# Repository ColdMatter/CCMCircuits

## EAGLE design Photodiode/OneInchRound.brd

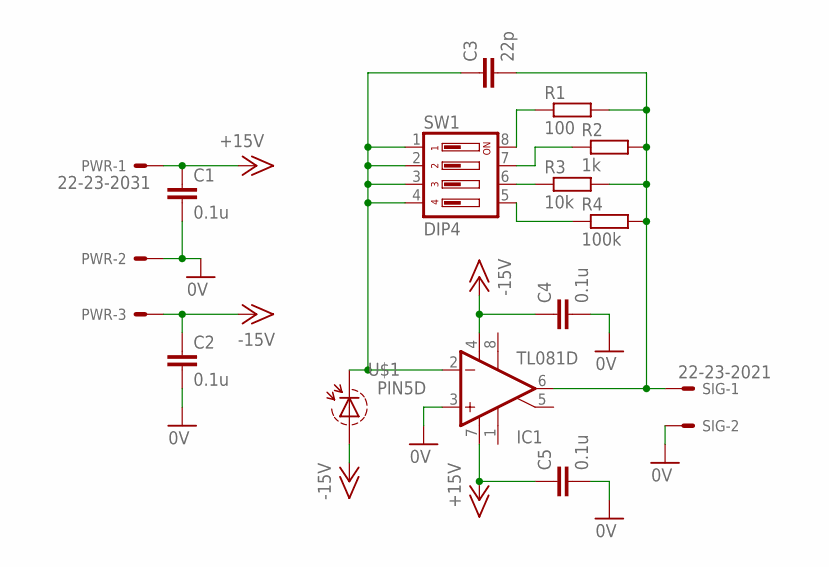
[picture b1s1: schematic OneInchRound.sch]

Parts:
C1, C2, C4, C5: 0.1u; C0805
C3: 22p; C0805
IC1: TL081D; SO08
PWR: 22-23-2031
R1: 100; R0805
R2: 1k; R0805
R3: 10k; R0805
R4: 100k; R0805
SIG: 22-23-2021
SW1: DIP4; SO08
U$1: PIN5D; TO5_2P

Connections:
0V: C1.2, C2.2, C4.2, C5.2, IC1.3 (+IN), PWR.2, SIG.2
+15V: C1.1, C5.1, IC1.7 (V+), PWR.1
-15V: C2.1, C4.1, IC1.4 (V-), PWR.3, U$1.1 (ANODE)
unnamed: C3.1, IC1.2 (-IN), SW1.1, SW1.2, SW1.3, SW1.4, U$1.3 (CATH)
unnamed: C3.2, IC1.6 (OUT), R1.2, R2.2, R3.2, R4.2, SIG.1
unnamed: R3.1, SW1.6
unnamed: R4.1, SW1.5
unnamed: R2.1, SW1.7
unnamed: R1.1, SW1.8

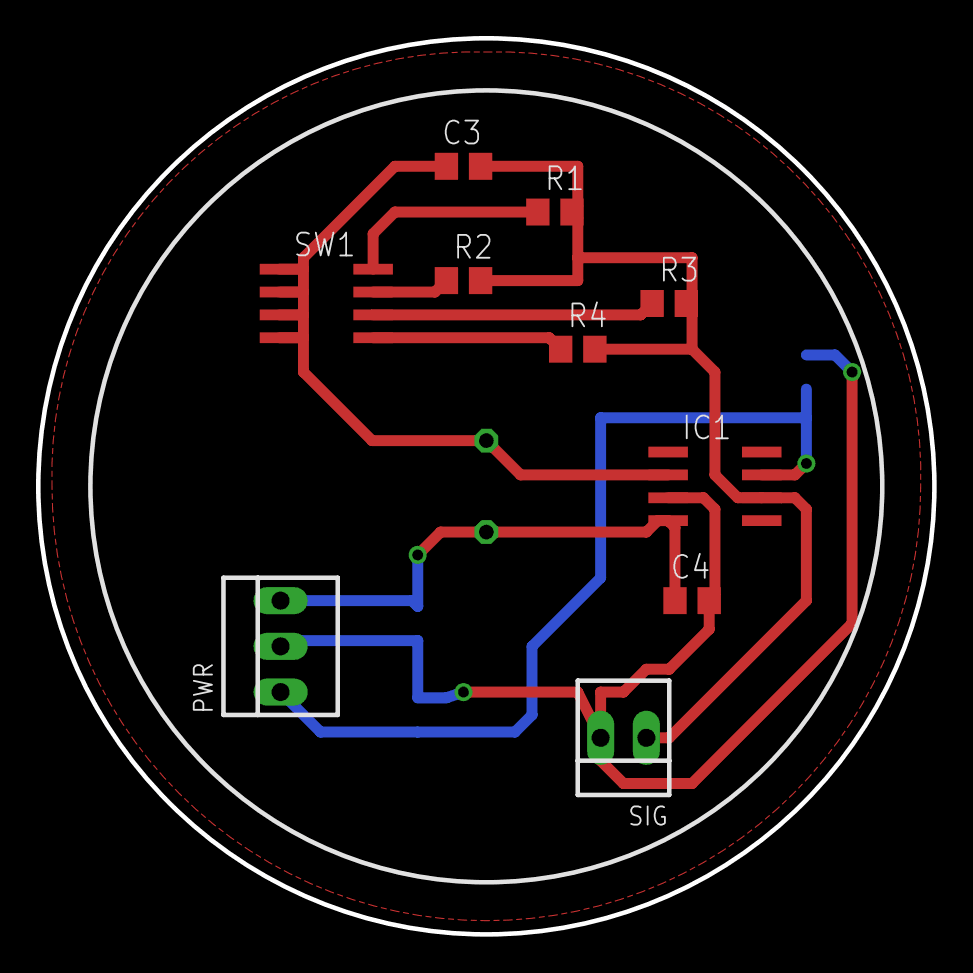
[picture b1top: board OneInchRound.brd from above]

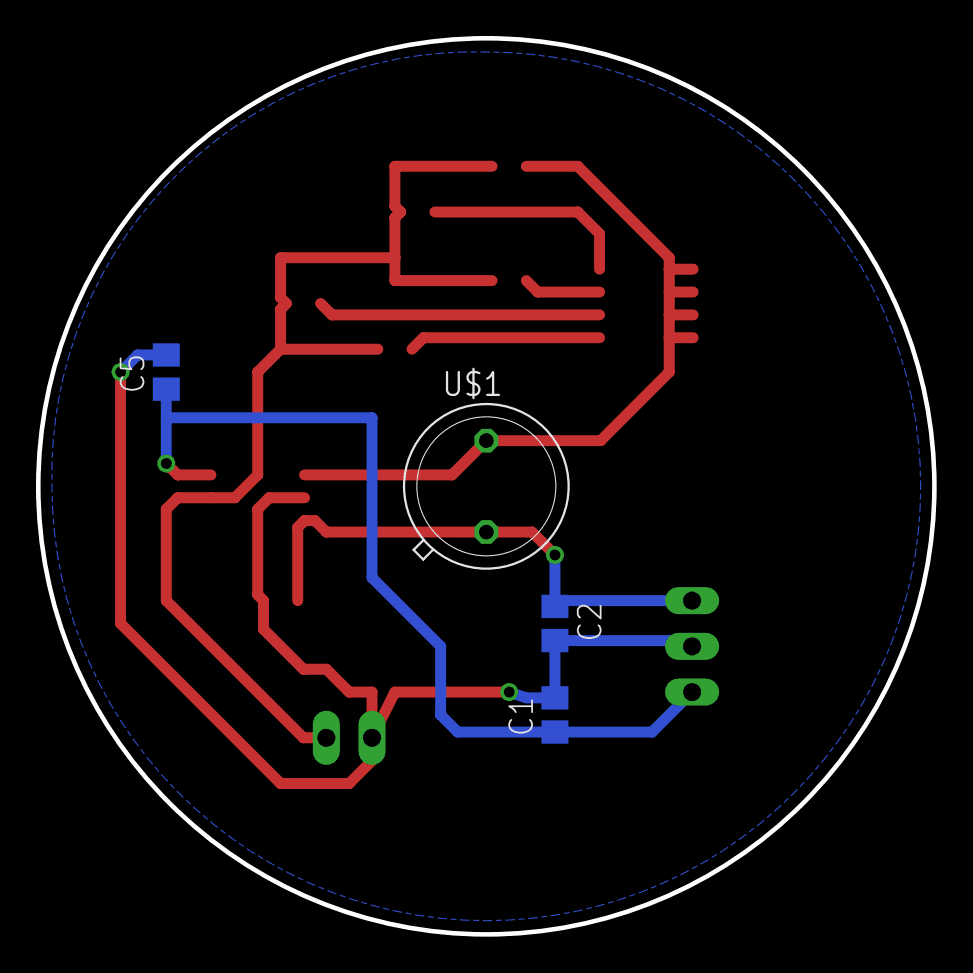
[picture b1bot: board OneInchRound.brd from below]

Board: 2 copper layers, 49.8 x 49.8 mm, 14 parts (4 on the bottom side), 9 nets.

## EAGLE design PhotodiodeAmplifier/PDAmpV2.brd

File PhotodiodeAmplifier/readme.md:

Photodiode Amplifier

This is a simple circuit to amplify a photodiode signal.

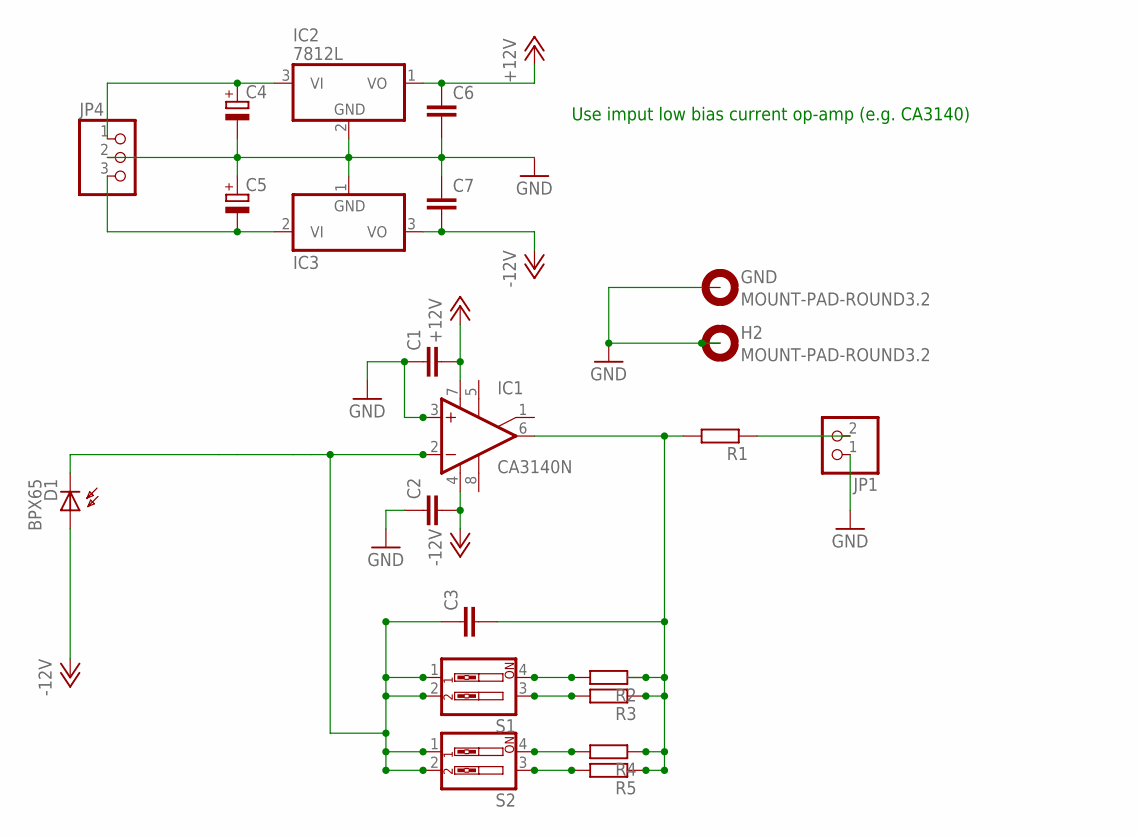
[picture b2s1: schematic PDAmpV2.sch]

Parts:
C1, C2: C-EU025-025X050; C025-025X050
C3, C6, C7: C-EU050-030X075; C050-030X075
C4, C5: CPOL-EUE5-8.5; E5-8,5
D1: BPX65
GND: MOUNT-PAD-ROUND3.2; 3,2-PAD
H2: MOUNT-PAD-ROUND3.2; 3,2-PAD
IC1: CA3140N; DIL08
IC2: 7812L; TO92
IC3: 7912L; TO92
JP1: PINHD-1X2; 1X02
JP4: PINHD-1X3; 1X03
R1, R2, R3, R4, R5: R-EU_0207/10; 0207/10
S1, S2: SW_DIP-2; EDG-02

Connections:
+12V: C1.2, C6.1, IC1.7 (V+), IC2.1 (VO)
-12V: C2.2, C7.2, D1.A, IC1.4 (V-), IC3.3 (VO)
GND: C1.1, C2.1, C4.-, C5.+, C6.2, C7.1, GND.B3,2, H2.B3,2, IC1.3 (+IN), IC2.2 (GND), IC3.1 (GND), JP1.1, JP4.2
unnamed: C3.1, D1.K (C), IC1.2 (-IN), S1.1, S1.2, S2.1, S2.2
unnamed: C4.+, IC2.3 (VI), JP4.1
unnamed: C5.-, IC3.2 (VI), JP4.3
unnamed: JP1.2, R1.1
unnamed: R2.2, S1.4
unnamed: R3.2, S1.3
unnamed: R4.2, S2.4
unnamed: R5.2, S2.3
unnamed: C3.2, IC1.6 (OUT), R1.2, R2.1, R3.1, R4.1, R5.1

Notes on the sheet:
Use imput low bias current op-amp (e.g. CA3140)

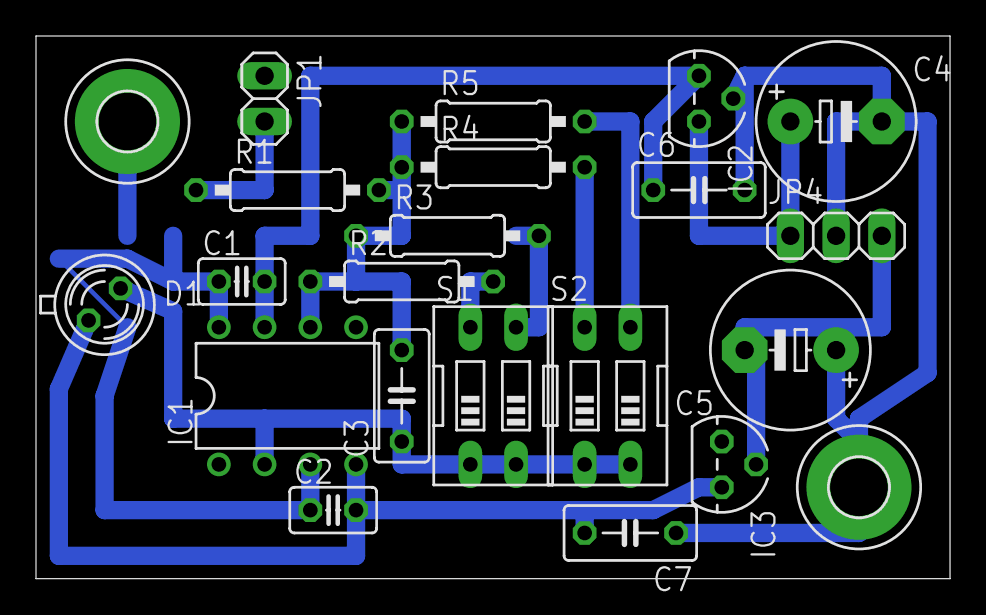
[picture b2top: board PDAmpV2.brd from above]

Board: 2 copper layers, 50.8 x 30.1 mm, 22 parts (0 on the bottom side), 12 nets.

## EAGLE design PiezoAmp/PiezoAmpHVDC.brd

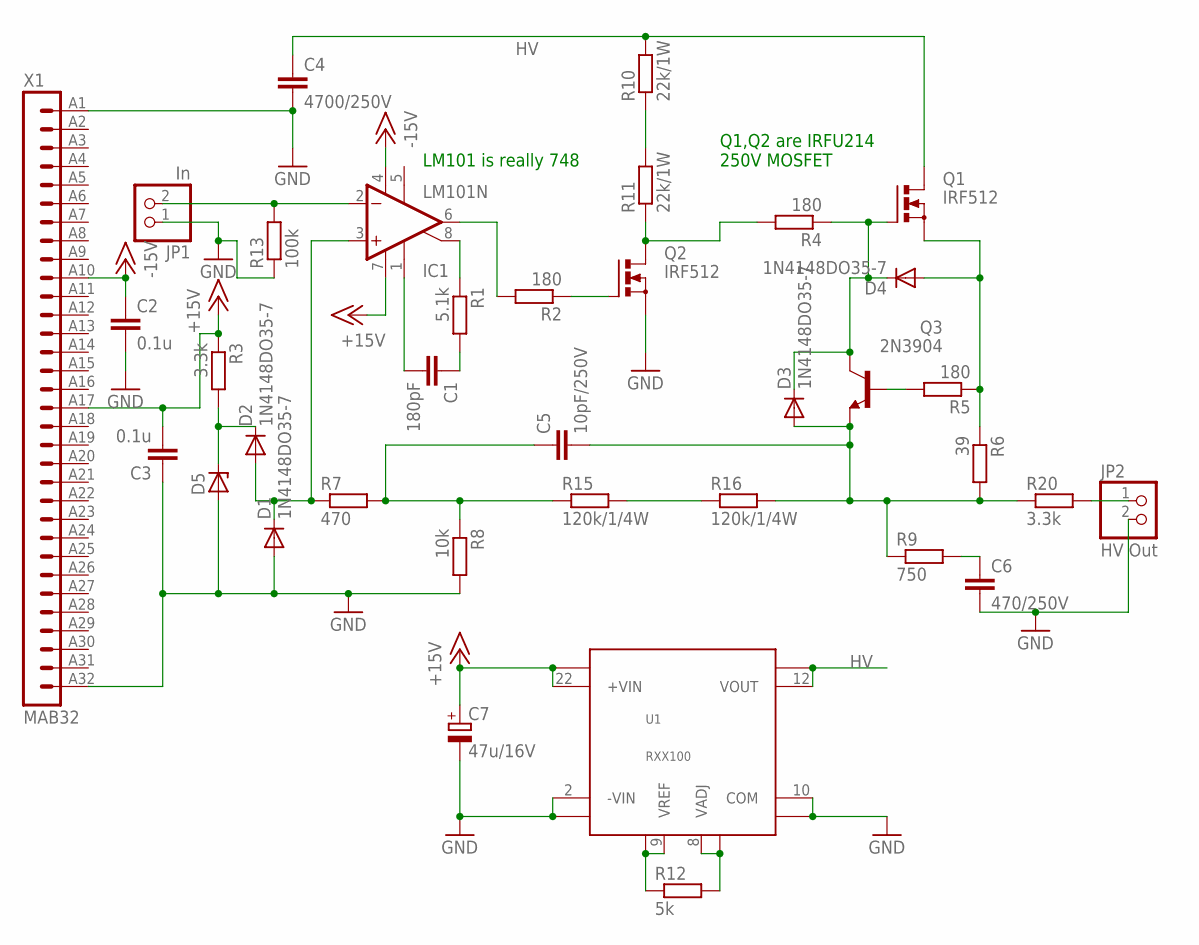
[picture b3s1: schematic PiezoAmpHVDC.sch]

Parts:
C1: 180pF; C050-030X075
C2, C3: 0.1u; C050-030X075
C4: 4700/250V; C075-032X103
C5: 10pF/250V; C075-032X103
C6: 470/250V; C075-032X103
C7: 47u/16V; SANYO-OSCON_F8
D1, D2, D3, D4: 1N4148DO35-7; DO35-7
D5: ZENER-DIODEDO34-7; DO34Z7
IC1: LM101N; DIL08
JP1: In; 1X02
JP2: HV Out; 1X02
Q1, Q2: IRF512; TO220BV
Q3: 2N3904; TO92
R1: 5.1k; 0204/7
R2, R4, R5: 180; 0204/7
R3, R20: 3.3k; 0204/7
R6: 39; 0204/7
R7: 470; 0204/7
R8: 10k; 0204/7
R9: 750; 0204/7
R10, R11: 22k/1W; 0411/15
R12: 5k; 0204/7
R13: 100k; 0204/5
R15, R16: 120k/1/4W; 0411/15
U1: RXX100; RXXDIP
X1: MAB32

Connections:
+15V: C3.2, C7.+, IC1.7 (V+), R3.1, U1.22 (+VIN), U1.23 (VIN2+), X1.A17 (17)
-15V: C2.1, IC1.4 (V-), X1.A10 (10)
GND: C2.2, C3.1, C4.2, C6.2, C7.-, D1.A, D5.A, JP1.1, JP2.2, Q2.S, R8.2, R13.1, U1.2 (-VIN), U1.3 (VIN2-), U1.10 (COM), U1.15 (COM2), X1.A1 (1), X1.A32 (32)
HV: C4.1, Q1.D, R10.2, U1.12 (VOUT), U1.13 (VOUT2)
unnamed: IC1.2 (-IN), JP1.2, R13.2
unnamed: R10.1, R11.2
unnamed: Q2.G, R2.1
unnamed: Q2.D, R4.2, R11.1
unnamed: C6.1, R9.2
unnamed: R12.2, U1.8 (VADJ), U1.17 (VADJ2)
unnamed: IC1.8 (ON2), R1.1
unnamed: IC1.6 (OUT), R2.2
unnamed: R12.1, U1.9 (VREF), U1.16 (VREF2)
unnamed: D3.C, D4.C, Q1.G, Q3.1 (C), R4.1
unnamed: D4.A, Q1.S, R5.1, R6.1
unnamed: Q3.2 (B), R5.2
unnamed: C5.2, D3.A, Q3.3 (E), R6.2, R9.1, R16.2, R20.1
unnamed: R15.2, R16.1
unnamed: C5.1, R7.2, R8.1, R15.1
unnamed: D1.C, D2.A, IC1.3 (+IN), R7.1
unnamed: D2.C, D5.C, R3.2
unnamed: JP2.1, R20.2
unnamed: C1.1, R1.2
unnamed: C1.2, IC1.1 (ON1)

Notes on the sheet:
Q1,Q2 are IRFU214 250V MOSFET
LM101 is really 748

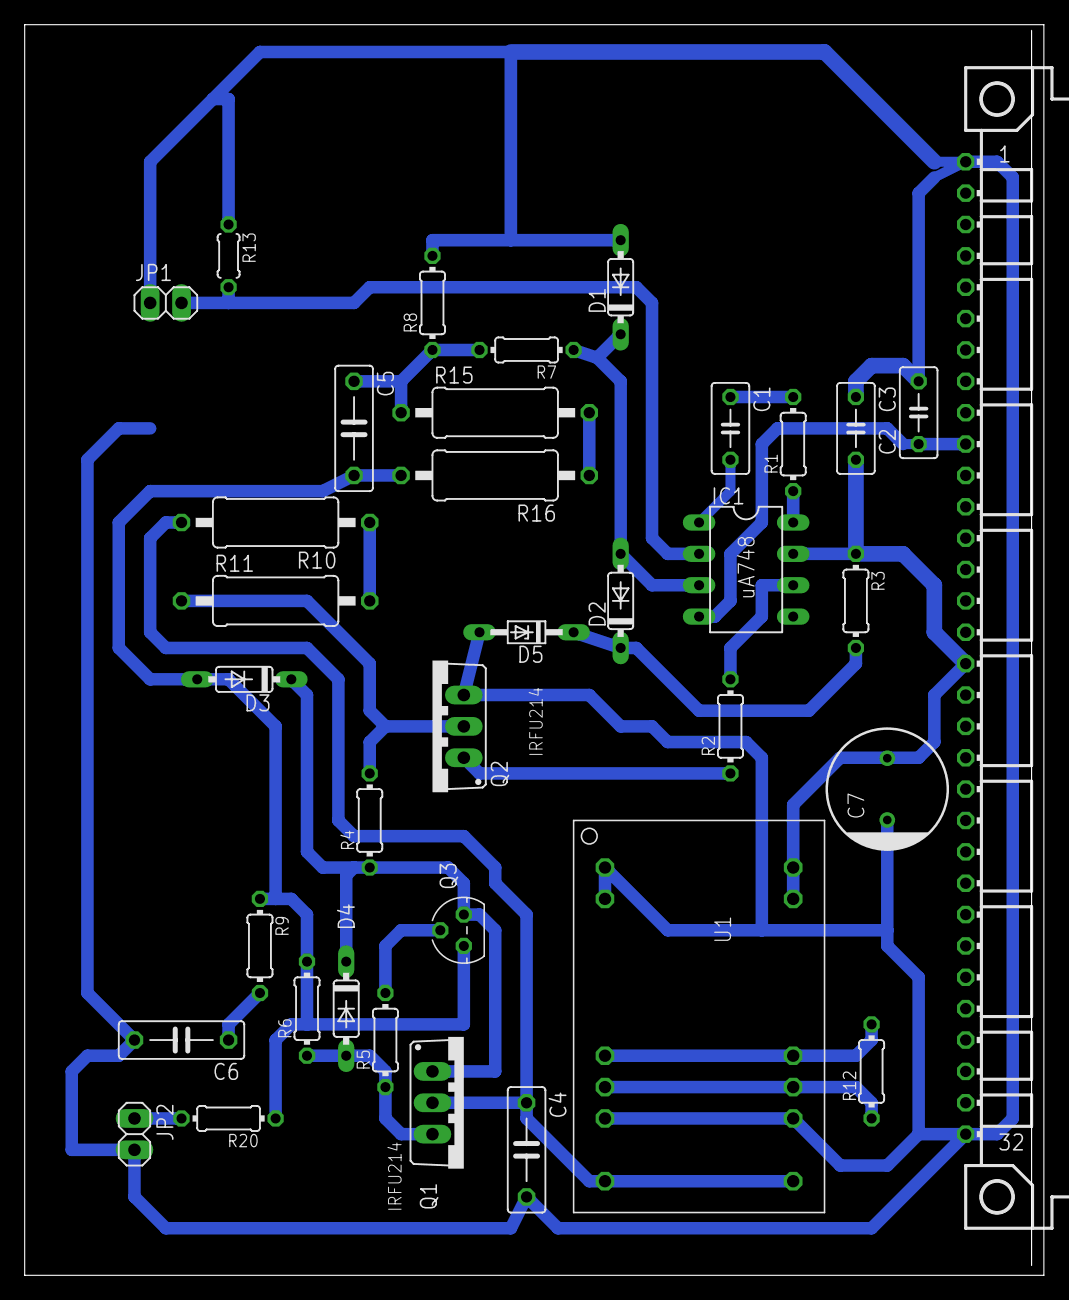
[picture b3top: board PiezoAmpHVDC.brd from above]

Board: 2 copper layers, 82.5 x 101.3 mm, 36 parts (0 on the bottom side), 24 nets.
